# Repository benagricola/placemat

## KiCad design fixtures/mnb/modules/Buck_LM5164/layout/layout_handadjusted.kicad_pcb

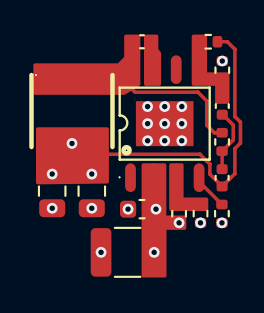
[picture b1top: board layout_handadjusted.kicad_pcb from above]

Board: 2 copper layers, 15 parts (0 on the bottom side), 9 nets.

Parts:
C1: GCM1555C1H102FA16D; C_0402_1005Metric
C2: GCM1555C1H221FA16D; C_0402_1005Metric
C3: GRM1555C1H222JA01D; C_0402_1005Metric
C4: GRM32EC72A106KE05L; C_1210_3225Metric
C5: GRM188R72A104KA35D; C_0603_1608Metric
C6, C7: TMK212BBJ106KGHT; C_0805_2012Metric
L1: SMNR4020-220M; IND-SMD_L4.0-W4.0_LQH44PN2R2MP0L
R1: ERJ-2RKF2403X; R_0402_1005Metric
R2: ERJ-2RKF1003X; R_0402_1005Metric
R3: ERJ-2RKF1004X; R_0402_1005Metric
R4: ERJ-2RKF4992X; R_0402_1005Metric
R5: ERJ-2RKF1583X; R_0402_1005Metric
R6: RC0402FR-0712K4L; R_0402_1005Metric
U1: LM5164DDAR; SO-8_L4.9-W3.9-P1.27-LS6.0-BL-EP

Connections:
BST: C3.1, U1.7
EN: R2.1, R3.2, U1.3
FB: C2.2, R4.1, R5.2, U1.5
RIPPLE: C1.1, C2.1, R1.2
RON: R6.1, U1.4
SW: C3.2, L1.1, R1.1, U1.8
gnd: C4.2, C5.2, C6.2, C7.2, R2.2, R4.2, R6.2, U1.1, U1.9
vin: C4.1, C5.1, R3.1, U1.2
vout: C1.2, C6.1, C7.1, L1.2, R5.1

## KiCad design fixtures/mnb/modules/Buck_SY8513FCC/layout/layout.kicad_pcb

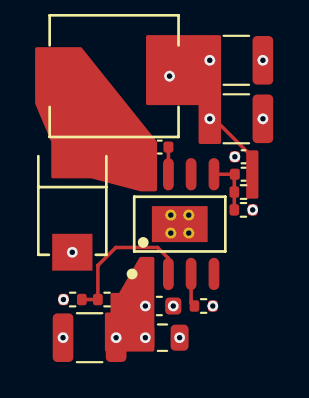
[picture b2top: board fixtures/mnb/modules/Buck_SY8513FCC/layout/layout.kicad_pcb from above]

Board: 2 copper layers, 16 parts (0 on the bottom side), 8 nets.

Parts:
C1, C8: GCM155R71H104KE02D; C_0402_1005Metric
C2: GCM1555C1H220FA16D; C_0402_1005Metric
C3: GRM21BC72A105KE01L; C_0805_2012Metric
C4: GRM32EC72A106ME05L; C_1210_3225Metric
C5: GRM188R72A104KA35D; C_0603_1608Metric
C6, C7: GMK325BJ226MM-T; C_1210_3225Metric
D1: SS510B; SMB_L4.6-W3.5-LS5.3-RD
L1: SMMS0630-220M; IND-SMD_L7.3-W6.6_MHCI06030
R1: ERJ-2RKF1003X; R_0402_1005Metric
R2: ERJ-2RKF1004X; R_0402_1005Metric
R3: ERJ-2RKF1002X; R_0402_1005Metric
R4: ERJ-2RKF5232X; R_0402_1005Metric
R5: ERJ-2RKF3323X; R_0402_1005Metric
U1: SY8513FCC; SOP-8_L4.9-W3.9-P1.27-LS6.0-BL-EP3.1

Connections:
BS: C1.1, U1.7
EN: R1.1, R2.2, U1.2
FB: C2.2, R3.1, R4.2, U1.5
FS: R5.1, U1.3
LX: C1.2, D1.1, L1.1, U1.8
gnd: C3.2, C4.2, C5.2, C6.2, C7.2, C8.2, D1.2, R1.2, R3.2, R5.2, U1.4, U1.9
vin: C3.1, C4.1, C5.1, R2.1, U1.1
vout: C2.1, C6.1, C7.1, C8.1, L1.2, R4.1

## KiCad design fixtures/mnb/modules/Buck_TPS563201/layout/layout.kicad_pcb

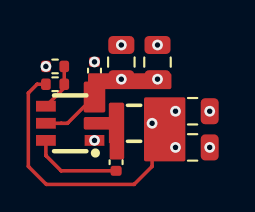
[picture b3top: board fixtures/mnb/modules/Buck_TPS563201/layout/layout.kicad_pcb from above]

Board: 2 copper layers, 10 parts (0 on the bottom side), 6 nets.

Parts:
C1, C4: GCM155R71H104KE02D; C_0402_1005Metric
C2, C3: CL21A106KOCLRNC; C_0805_2012Metric
C5, C6: CL21A226MPQNNNE; C_0805_2012Metric
L1: FTC252012S2R2MBCA; IND-SMD_L2.5-W2.0_MHCHL2520
R1: ERJ-2RKF1002X; R_0402_1005Metric
R2: ERJ-2RKF3302X; R_0402_1005Metric
U1: TPS563201DDCR; SOT-23-6_L2.9-W1.6-P0.95-LS2.8-BR

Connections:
SW: C1.2, L1.1, U1.2
VBST: C1.1, U1.6
VFB: R1.1, R2.2, U1.4
gnd: C2.2, C3.2, C4.2, C5.2, C6.2, R1.2, U1.1
vin: C2.1, C3.1, C4.1, U1.3, U1.5
vout: C5.1, C6.1, L1.2, R2.1

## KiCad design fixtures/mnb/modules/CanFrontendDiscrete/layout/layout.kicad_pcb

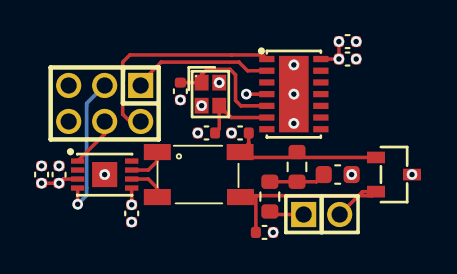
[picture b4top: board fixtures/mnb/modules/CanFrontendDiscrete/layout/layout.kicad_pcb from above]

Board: 2 copper layers, 19 parts (0 on the bottom side), 15 nets.

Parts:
C1, C8: CL05A105KP5NNNC; C_0402_1005Metric
C2, C9, C10: GCM155R71H104KE02D; C_0402_1005Metric
C3, C4: CC0402JRNPO9BN330; C_0402_1005Metric
C5, C6: 10pF; C_0402_1005Metric
C7: CL10B472KB8NNNC; C_0603_1608Metric
D1: PESD2CAN,215; SOT-23-3_L2.9-W1.3-P1.90-LS2.4-BR
H1: X4621WV-2x03I-C40D28; HDR-TH_6P-P2.00-V-M-R2-C3-S2.00
H2: PZ200V-11-02P; HDR-TH_2P-P2.00-V-M
L1: ACT45B-110-2P-TL003; FILTER-SMD_4P-L4.5-W3.2-TL-2
R1, R2: ERJ-3EKF60R4V; R_0603_1608Metric
U1: MCP2518FDT-E/QBB; VDFN-14_L4.5-W3.0-P0.65-BL-EP
U2: MCP2542WFDT-H/MNY; TDFN-8_L3.0-W2.0-P0.50-BL-EP1.4
X1: XTM20040000FT00351001; CRYSTAL-SMD_4P-L2.0-W1.6-BL-A

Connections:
CAN_N: C5.1, D1.2, H2.2, L1.3
CAN_P: C6.1, D1.1, L1.4, R1.1
CAN_TX_N: L1.2, U2.6
CAN_TX_P: L1.1, U2.7
CTRL_RXCAN: H1.1, U1.2
CTRL_TXCAN: H1.2, U1.1
OSC1: C3.1, U1.6, X1.3
OSC2: C4.1, U1.5, X1.1
TERM_JLEG: H2.1, R2.2
TERM_MID: C7.1, R1.2, R2.1
XCVR_RXD: H1.3, U2.4
XCVR_TXD: H1.4, U2.1
gnd: C1.2, C2.2, C3.2, C4.2, C5.2, C6.2, C7.2, C8.2, C9.2, C10.2, D1.3, U1.7, U1.15, U2.2, U2.8, U2.9, X1.2, X1.4
v3v3: C1.1, C2.1, C10.1, U1.14, U2.5
v5: C8.1, C9.1, U2.3

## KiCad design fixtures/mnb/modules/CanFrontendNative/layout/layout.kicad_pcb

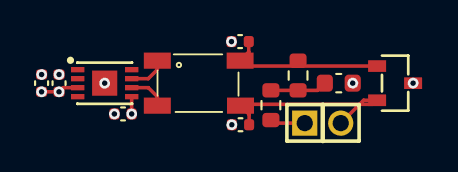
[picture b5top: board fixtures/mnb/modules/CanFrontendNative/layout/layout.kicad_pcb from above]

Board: 2 copper layers, 12 parts (0 on the bottom side), 9 nets.

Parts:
C1, C2: 10pF; C_0402_1005Metric
C3: CL10B472KB8NNNC; C_0603_1608Metric
C4: C0402C105K9PACTU; C_0402_1005Metric
C5, C6: GCM155R71H104KE02D; C_0402_1005Metric
D1: PESD2CAN,215; SOT-23-3_L2.9-W1.3-P1.90-LS2.4-BR
H1: PZ200V-11-02P; HDR-TH_2P-P2.00-V-M
L1: ACT45B-110-2P-TL003; FILTER-SMD_4P-L4.5-W3.2-TL-2
R1, R2: ERJ-3EKF60R4V; R_0603_1608Metric
U1: MCP2542WFDT-H/MNY; TDFN-8_L3.0-W2.0-P0.50-BL-EP1.4

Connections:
CAN_N: C1.1, D1.2, H1.2, L1.3
CAN_P: C2.1, D1.1, L1.4, R1.1
CAN_TX_N: L1.2, U1.6
CAN_TX_P: L1.1, U1.7
TERM_JLEG: H1.1, R2.2
TERM_MID: C3.1, R1.2, R2.1
gnd: C1.2, C2.2, C3.2, C4.2, C5.2, C6.2, D1.3, U1.2, U1.8, U1.9
v3v3: C6.1, U1.5
v5: C4.1, C5.1, U1.3

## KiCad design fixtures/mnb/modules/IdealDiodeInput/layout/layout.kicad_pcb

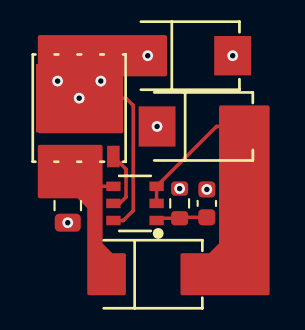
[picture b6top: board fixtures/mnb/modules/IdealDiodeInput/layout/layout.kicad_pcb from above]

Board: 2 copper layers, 8 parts (0 on the bottom side), 6 nets.

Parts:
C1: GRM21BC72A105KE01L; C_0805_2012Metric
C2: GRM188R72A104KA35D; C_0603_1608Metric
D1, D2: SS510B; SMB_L4.6-W3.5-LS5.3-RD
D3: SMBJ58A-TR; SMB_L4.6-W3.6-LS5.3-RD
Q1: HYG053N10NS1C2; PDFN-8_L5.8-W5.0-P1.27-LS6.2-BL
R1: ERJ-3EKF1000V; R_0603_1608Metric
U1: LM5050MK-1/NOPB; TSOT-23-6_L2.9-W1.6-P0.95-LS2.8-BR

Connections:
GATE: Q1.4, U1.5
GND_FLOAT: D1.2, D2.2, U1.2, U1.3
VS: C2.1, R1.2, U1.1
gnd: C1.2, C2.2, D1.1, D3.2
vin_raw: C1.1, D2.1, Q1.1, Q1.2, Q1.3, U1.4
vout: D3.1, Q1.5, Q1.6, Q1.7, Q1.8, Q1.9, R1.1, U1.6

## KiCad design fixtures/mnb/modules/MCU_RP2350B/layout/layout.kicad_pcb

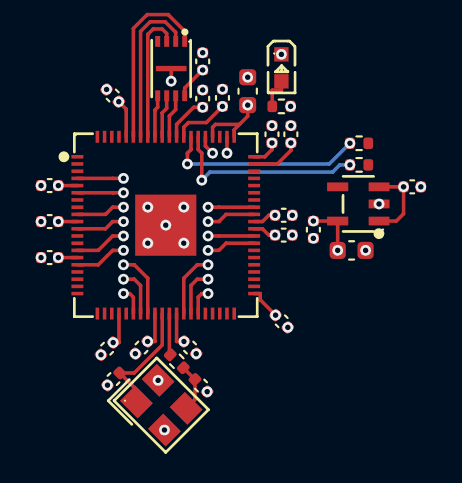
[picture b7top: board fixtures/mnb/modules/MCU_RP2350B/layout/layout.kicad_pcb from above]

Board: 2 copper layers, 30 parts (0 on the bottom side), 15 nets.

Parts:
C1, C2, C3, C4, C5, C6, C7, C8, C9, C10, C11, C12, C13, C16, C17: GCM155R71H104KE02D; C_0402_1005Metric
C14, C15: CL05A105KP5NNNC; C_0402_1005Metric
C18, C19: JMK107C6475MA-T; C_0603_1608Metric
C20, C21: GCM1555C1H150FA16D; C_0402_1005Metric
D1: KT-0603G; LED0603-RD_C12624
R1: ERJ-2RKF4700X; R_0402_1005Metric
R2, R3: ERJ-2RKF27R0X; R_0402_1005Metric
R4: ERJ-2RKF1001X; R_0402_1005Metric
U1: W25Q16JVUXIQ; USON-8_L3.0-W2.0-P0.50-BL-EP
U2: RP2350B; QFN-80_L10.0-W10.0-P0.40-TL-EP3.4
U3: TLV74311PDBVR; SOT-23-5_L3.0-W1.7-P0.95-LS2.8-BL
Y1: ABM8-272-T3; CRYSTAL-SMD_4P-L3.2-W2.5-BL

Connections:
LED_PWR_NODE: D1.2, R1.2
OSC_XIN: C20.1, U2.30, Y1.1
OSC_XOUT: R4.2, U2.31
OSC_Y_XOUT: C21.1, R4.1, Y1.3
QSPI_SCLK: U1.6, U2.71
QSPI_SD0: U1.5, U2.72
QSPI_SD1: U1.2, U2.74
QSPI_SD2: U1.3, U2.73
QSPI_SD3: U1.7, U2.70
QSPI_SS: U1.1, U2.75
USB_MCU_N: R2.1, U2.66
USB_MCU_P: R3.1, U2.67
V1V1: C2.1, C3.1, C4.1, C15.1, C18.1, U2.10, U2.32, U2.51, U3.5
gnd: C1.2, C2.2, C3.2, C4.2, C5.2, C6.2, C7.2, C8.2, C9.2, C10.2, C11.2, C12.2, C13.2, C14.2, C15.2, C16.2, C17.2, C18.2, C19.2, C20.2, C21.2, D1.1, U1.4, U1.9, U2.62, U2.65, U2.81, U3.2, Y1.2, Y1.4
v3v3: C1.1, C5.1, C6.1, C7.1, C8.1, C9.1, C10.1, C11.1, C12.1, C13.1, C14.1, C16.1, C17.1, C19.1, R1.1, U1.8, U2.5, U2.15, U2.24, U2.29, U2.41, U2.50, U2.59, U2.60, U2.61, U2.64, U2.68, U2.69, U2.76, U3.1, U3.3
